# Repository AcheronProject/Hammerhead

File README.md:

# Acheron 40-SM-S-STM32-MXSM-TH-WI (Codename "Hammerhead")

See [this page](https://gondolindrim.github.io/AcheronDocs/hammerhead/intro.html) for the Hammerhead documentation.

## Introduction

The Hammerhead is named after the SharkPCB; in order to differentiate Hammerhead (which features a staggered layout) from the Shark (which features an ortho layout), I renamed the staggered version like so.

This PCB was born as a replacement PCB for an AMJ40 keyboard I have. I bought it from a user on r/mechmarket for a fairly cheap price, since the stock kit PCB was not working due to that previous owner using a Dremel tool and breaking a few traces on the PCB. After fixing the stock PCB it did work for three years, and I set myself to devise another PCB for it. As such, Hammerhead is fully compatible with the AMJ40 case.

## Supported layouts

Click [this link](http://www.keyboard-layout-editor.com/#/gists/89c3a984e836b351fcaf27332abd0f3e) for the KLE file for the Hammerhead.

## Renders

Click at the images to zoom in.

Renders generated by the [tracespace.io](https://tracespace.io/view/) site.

## Copyright notice

This project is released under the Acheron Open-Hardware Licence V1.1. For the license, please refer to the LICENCE.md file.

The Hammherhead icon used is a free-to-used icon that I downloaded from [this link](https://www.flaticon.com/free-icon/hammerhead-fish-shape_47439#term=hammerhead&page=1&position=2) at Freepik.com .

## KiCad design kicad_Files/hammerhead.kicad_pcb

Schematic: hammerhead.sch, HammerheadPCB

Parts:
CB1: 1uF; C_0402_1005Metric
CB2: 10n; C_0402_1005Metric
CB3, CB5, CB8: 100n; C_0402_1005Metric
CB4, CB6: 4.7uF; C_0402_1005Metric
CB7: 100nF; C_0402_1005Metric
CD1: 4.7nF; C_0805_2012Metric
CRST1: 10u; C_0805_2012Metric_Pad1.15x1.40mm_HandSolder
CRST2: 4.7n; C_0805_2012Metric_Pad1.15x1.40mm_HandSolder
CSH1: 4.7nF; C_0805_2012Metric
CSI1: 10u; C_0805_2012Metric_Pad1.15x1.40mm_HandSolder
CSO1: 1u; C_0805_2012Metric_Pad1.15x1.40mm_HandSolder
D1, D2, D3, D4, D5, D6, D7, D8, D9, D10, D11, D12, D13, D14, D15, D16, D17, D18, D19, D20, D21, D22, D23, D24, D25, D26, D27, D28, D29, D30, D31, D32, D33, D34, D35, D36, D37, D38, D39, D40, D43, D45: 1N4148; D_SOD-123
DD1: 1N4007; D_SOD-123
DF1: RB060M-60TR; D_SOD-123
DRST1: 1N4148; D_SOD-123
DS1: 1N4007; D_SOD-123
F1: Polyfuse; Fuse_1812_4532
H1, H6: Half Side Hole; halfSideHole
H2: Mounting Hole; MoutingHole_Oval_7mm_5.0x2.5mm
H3, H4, H5, H7: Oval Mounting Hole; MoutingHole_Oval_7mm_5.0x2.5mm
J1: TYPE-C-31-M12_13; TYPE-C-31-M-12
J2: Conn_ARM_JTAG_SWD_10
J3: Conn_01x08; PinHeader_1x8_P2.54mm_Vertical
J4: Conn_01x08; PinHeader_1x10_P2.54mm_Vertical
L1: HammerheadLogo; hammerhead_Logo
L2: OSHLogo; osh-logo
L3: Acheron Logo; acheronLong
QRST1: DTC123J; SOT-23
RCC1, RCC2: 5.1k; R_0402_1005Metric
RD1: 1M; R_0805_2012Metric
RF1: 10k; R_SMD_1026
RRST1: 100k; R_SMD_1026
RSH1: 1M; R_0805_2012Metric
SW1: ESC; MX100
SW2: Q; MX100
SW3: W; MX100
SW4: E; MX100
SW5: R; MX100
SW6: T; MX100
SW7: Y; MX100
SW8: U; MX100
SW9: I; MX100
SW10: O; MX100
SW11: P; MX100
SW12: BKSP; MX100
SW13: TAB_125; MX125
SW14: A; MX100
SW15: S; MX100
SW16: D; MX100
SW17: F; MX100
SW18: G; MX100
SW19: H; MX100
SW20: J; MX100
SW21: K; MX100
SW22: L; MX100
SW23: ENTER_175; MX175
SW24: LSHIFT_175; MX175
SW25: Z; MX100
SW26: X; MX100
SW27: C; MX100
SW28: V; MX100
SW29: B; MX100
SW30: N; MX100
SW31: M; MX100
SW32: /?; MX100
SW33: RSHIFT_125; MX125
SW34: FN_100; MX100
SW35: RSHIFT_225; MX225
SW36, SW46: SUPER_100; MX100
SW37: LALT_100; MX100
SW38: SPC_625; MX625R
SW39, SW45: RALT_125; MX125
SW40: LCTRL_125; MX125
SW41: RCTRL_125; MX125
SW42: LALT_125; MX125
SW43: SPC_225; MX225R
SW44: SPC_275; MX275R
SWRST1: SW_Push; smdPushBtn
U1: STM32F072-LQFP48; LQFP-48_7x7mm_P0.5mm
U2: USBLC6-2SC6; SOT-23-6
U3: MCP1700-3302E_SOT23; SOT-23

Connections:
3.3V: CB1.2, CB2.2, CB3.2, CB4.2, CB5.2, CB6.2, CB7.1, CB8.2, CSO1.2, DS1.2 (A), J2.1 (VTref), SWRST1.1, U1.1 (VBAT), U1.9 (VDDA), U1.24 (VDD), U1.36 (VDDIO2), U1.48 (VDD), U3.2 (VO)
5V: CSI1.2, DF1.1 (K), DS1.1 (K), F1.1, RF1.2, U3.3 (VI)
/SHIELD: CSH1.2, J1.S (SHIELD), RSH1.1
BOOT0: CRST1.2, DRST1.1 (K), RRST1.2, U1.44 (BOOT0)
CASE: DD1.2 (A), H5.1
Col1: SW1.1 (Col), SW13.1 (Col), SW24.1 (Col), SW40.1 (Col), U1.42 (I2C1_SCL/PB6)
Col2: SW2.1 (Col), SW14.1 (Col), SW25.1 (Col), SW36.1 (Col), U1.15 (PA5/ADC_IN5/DAC_OUT2)
Col3: SW3.1 (Col), SW15.1 (Col), SW26.1 (Col), SW37.1 (Col), SW42.1 (Col), U1.14 (PA4/TIM14_CH1/ADC_IN4)
Col4: SW4.1 (Col), SW16.1 (Col), SW27.1 (Col), SW44.1 (Col), U1.13 (PA3/TIM15_CH2/ADC_IN3)
Col5: SW5.1 (Col), SW17.1 (Col), SW28.1 (Col), U1.12 (PA2/ADC_IN2)
Col6: SW6.1 (Col), SW18.1 (Col), SW29.1 (Col), SW38.1 (Col), SW43.1 (Col), U1.11 (PA1/ADC_IN1)
Col7: SW7.1 (Col), SW19.1 (Col), SW30.1 (Col), U1.10 (PA0/ADC_IN0)
Col8: SW8.1 (Col), SW20.1 (Col), SW31.1 (Col), SW45.1 (Col), U1.6 (PF1/OSC_OUT)
Col9: SW9.1 (Col), SW21.1 (Col), SW32.1 (Col), SW39.1 (Col), SW46.1 (Col), U1.5 (PF0/OSC_IN)
Col10: SW10.1 (Col), SW22.1 (Col), SW33.1 (Col), SW41.1 (Col), U1.4 (PC15/OSC32_OUT)
Col11: SW11.1 (Col), SW12.1 (Col), SW23.1 (Col), SW34.1 (Col), SW35.1 (Col), U1.3 (PC14/OSC32_IN)
D+: U1.33 (USB_DP/PA12), U2.3 (IO2)
D-: U1.32 (USB_DM/TIM1_CH4/PA11), U2.1 (IO1)
DBus+: J1.A7 (D-), J1.B7 (D-), U2.4 (IO2)
DBus-: J1.A6 (D+), J1.B6 (D+), U2.6 (IO1)
Extra1: J3.1, U1.41 (SPI1_MOSI/I2S1_SD/TIM3_CH2/PB5)
Extra2: J3.2, U1.40 (SPI1_MISO/I2S1_MCK/TIM3_CH1/PB4)
Extra3: J3.3, U1.39 (SPI1_SCK/I2S1_CK/TIM2_CH2/PB3)
Extra4: J3.4, U1.38 (PA2)
Extra5: J3.5, U1.31 (TIM1_CH3/PA10)
Extra6: J3.6, U1.30 (TIM1_CH2/PA9)
Extra7: J3.7, U1.29 (TIM1_CH1/PA8)
Extra8: J3.8, U1.28 (SPI2_MOSI/I2S2_SD/PB15)
Extra9: J4.1, U1.27 (PB14/SPI2_MISO/I2S2_MCK/I2C2_SDA/TIM15_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)
Extra10: J4.2, U1.26 (SPI2_SCK/I2S2_CK/I2C2_SCL/PB13)
Extra11: J4.3, U1.25 (PB12)
Extra12: J4.4, U1.22 (PB11/TIM2_CH4/I2C2_SDA)
Extra13: J4.5, U1.21 (PB10/SPI2_SCK/I2C2_SCL/TIM2_CH3)
Extra14: J4.6, U1.20 (PB2)
Extra15: J4.7, U1.19 (PB1/TIM3_CH4/TIM14_CH1/ADC_IN9)
Extra16: J4.8, U1.18 (PB0/TIM3_CH3/ADC_IN8)
Extra17: J4.9, U1.17 (PA7/TIM3_CH2/TIM14_CH1/ADC_IN7)
Extra18: J4.10, U1.16 (PA6/ADC_IN6/TIM3_CH1/TIM16_CH1)
GND: CB1.1, CB2.1, CB3.1, CB4.1, CB5.1, CB6.1, CB7.2, CB8.1, CD1.1, CRST1.1, CRST2.2, CSH1.1, CSI1.1, CSO1.1, DF1.2 (A), J1.A1 (GND), J1.B1 (GND), J2.3 (GND), J2.5 (GND), J2.9 (GNDDetect), QRST1.2 (E), RCC1.1, RCC2.1, RD1.2, RF1.1, RRST1.1, RSH1.2, U1.8 (VSSA), U1.23 (VSS), U1.35 (VSS), U1.47 (VSS), U2.2 (GND), U3.1 (GND)
NRST: CRST2.1, J2.10 (~RESET~), QRST1.3 (C), U1.7 (NRST)
unnamed: CD1.2, DD1.1 (K), RD1.1
unnamed: D1.2 (A), SW1.2 (Row)
unnamed: D2.2 (A), SW2.2 (Row)
unnamed: D3.2 (A), SW3.2 (Row)
unnamed: D4.2 (A), SW4.2 (Row)
unnamed: D5.2 (A), SW5.2 (Row)
unnamed: D6.2 (A), SW6.2 (Row)
unnamed: D7.2 (A), SW7.2 (Row)
unnamed: D8.2 (A), SW8.2 (Row)
unnamed: D9.2 (A), SW9.2 (Row)
unnamed: D10.2 (A), SW10.2 (Row)
unnamed: D11.2 (A), SW11.2 (Row)
unnamed: D12.2 (A), SW12.2 (Row)
unnamed: D13.2 (A), SW13.2 (Row)
unnamed: D14.2 (A), SW14.2 (Row)
unnamed: D15.2 (A), SW15.2 (Row)
unnamed: D16.2 (A), SW16.2 (Row)
unnamed: D17.2 (A), SW17.2 (Row)
unnamed: D18.2 (A), SW18.2 (Row)
unnamed: D19.2 (A), SW19.2 (Row)
unnamed: D20.2 (A), SW20.2 (Row)
unnamed: D21.2 (A), SW21.2 (Row)
unnamed: D22.2 (A), SW22.2 (Row)
unnamed: D23.2 (A), SW23.2 (Row)
unnamed: D24.2 (A), SW24.2 (Row)
unnamed: D25.2 (A), SW25.2 (Row)
unnamed: D26.2 (A), SW26.2 (Row)
unnamed: D27.2 (A), SW27.2 (Row)
unnamed: D28.2 (A), SW28.2 (Row)
unnamed: D29.2 (A), SW29.2 (Row)
unnamed: D30.2 (A), SW30.2 (Row)
unnamed: D31.2 (A), SW31.2 (Row)
unnamed: D32.2 (A), SW32.2 (Row)
unnamed: D33.2 (A), SW33.2 (Row)
unnamed: D34.2 (A), SW34.2 (Row), SW35.2 (Row)
unnamed: D35.2 (A), SW40.2 (Row)
unnamed: D36.2 (A), SW36.2 (Row)
unnamed: D37.2 (A), SW37.2 (Row), SW42.2 (Row)
unnamed: D38.2 (A), SW38.2 (Row), SW43.2 (Row)
unnamed: D39.2 (A), SW39.2 (Row), SW46.2 (Row)
unnamed: D40.2 (A), SW41.2 (Row)
unnamed: D43.2 (A), SW44.2 (Row)
unnamed: D45.2 (A), SW45.2 (Row)
unnamed: DRST1.2 (A), QRST1.1 (B), SWRST1.2
unnamed: J1.A5 (CC1), RCC1.2
unnamed: J1.B5 (CC2), RCC2.2
Row1: D1.1 (K), D2.1 (K), D3.1 (K), D4.1 (K), D5.1 (K), D6.1 (K), D7.1 (K), D8.1 (K), D9.1 (K), D10.1 (K), D11.1 (K), U1.43 (2C1_SDA/PB7)
Row2: D13.1 (K), D14.1 (K), D15.1 (K), D16.1 (K), D17.1 (K), D18.1 (K), D19.1 (K), D20.1 (K), D21.1 (K), D22.1 (K), D23.1 (K), U1.45 (I2C1_SCL/TIM16_CH1/PB8)
Row3: D24.1 (K), D25.1 (K), D26.1 (K), D27.1 (K), D28.1 (K), D29.1 (K), D30.1 (K), D31.1 (K), D32.1 (K), D33.1 (K), D34.1 (K), U1.2 (PC13)
Row4: D12.1 (K), D35.1 (K), D36.1 (K), D37.1 (K), D38.1 (K), D39.1 (K), D40.1 (K), D43.1 (K), D45.1 (K), U1.46 (SPI2_NSS/I2S2_WS/I2C1_SDA/TIM17_CH1/PB9)
SWCLK: J2.4 (SWDCLK/TCK), U1.37 (SWCLK/PA14)
SWDIO: J2.2 (SWDIO/TMS), U1.34 (SWDIO/PA13)
VBUS: F1.2, J1.A4 (VBUS), J1.B4 (VBUS), U2.5 (VBUS)

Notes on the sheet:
Hard reset circuit
Power supply and protection circuit
Logos and flags
Serial programming
[1] STM32F072x8 / STM32F072xB datasheet
REFERENCES
https://www.st.com/resource/en/datasheet/stm32f072rb.pdf
[2] AN4080 Application note
https://www.st.com/content/ccc/resource/technical/document/application_note/c9/19/d7/b8/6b/0e/4c/d3/DM00051986.pdf/files/DM00051986.pdf/jcr:content/translations/en.DM00051986.pdf
MCU
USB Connector
Shield
USD ESD
CBx are the bypass capacitors. Their value is specified in reference [2].
Case ESD

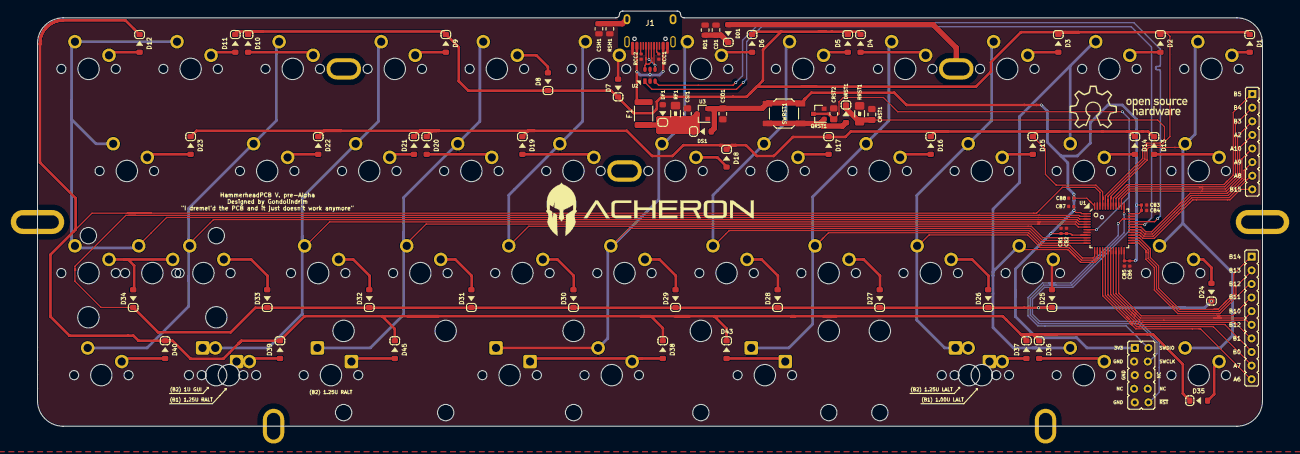
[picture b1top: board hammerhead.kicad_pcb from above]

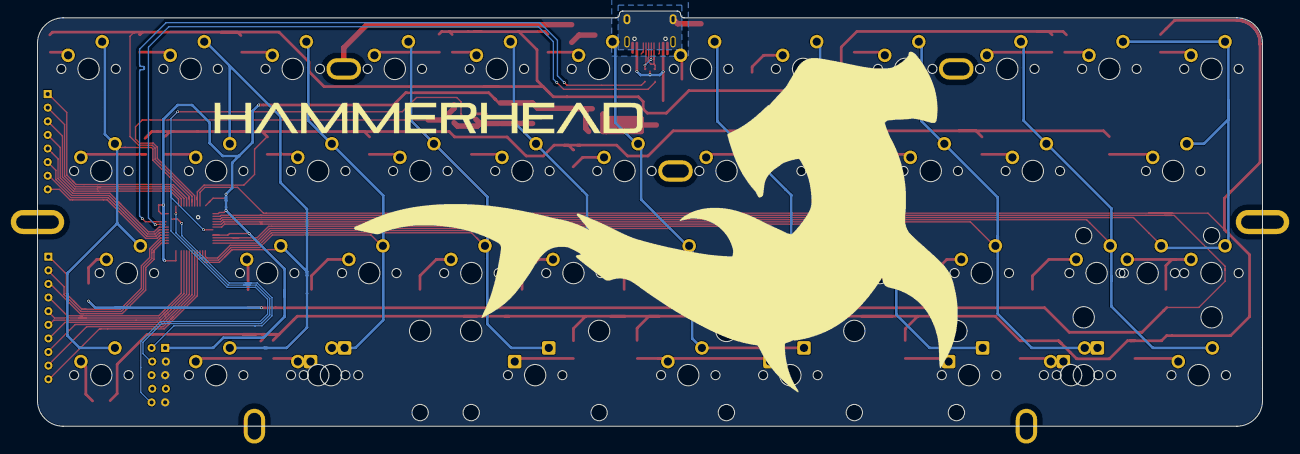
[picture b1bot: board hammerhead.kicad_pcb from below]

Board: 2 copper layers, 228.6 x 77.5 mm, 132 parts (8 on the bottom side), 93 nets.

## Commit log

2019-09-14 Finished routing
2019-09-14 Fixed REDME render links
2019-09-23 Added extra pins breakouts
2019-09-23 Updated renders and README
2019-09-23 Updated REAME broken link
2019-09-23 Updt: preparations for pre-Alpha release
